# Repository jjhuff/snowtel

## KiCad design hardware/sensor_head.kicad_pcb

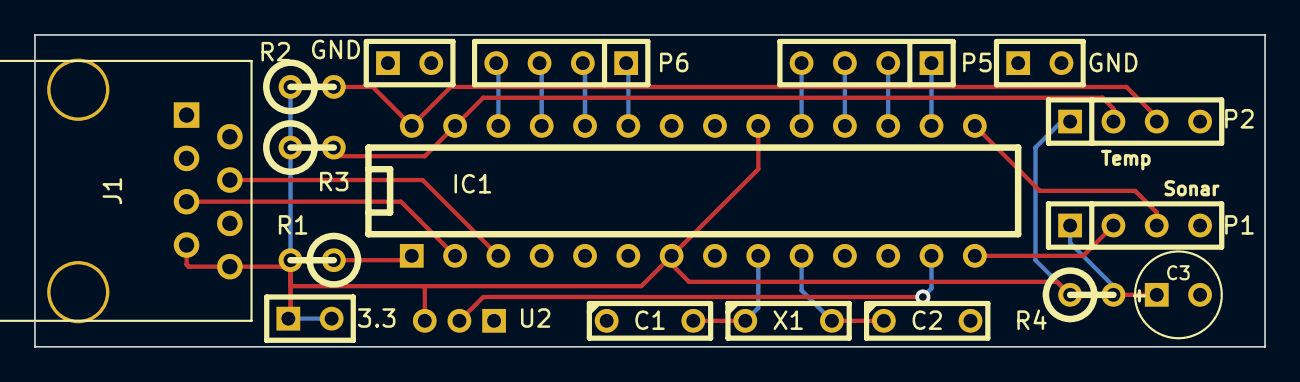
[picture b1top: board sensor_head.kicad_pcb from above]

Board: 2 copper layers, 72.1 x 18.3 mm, 18 parts (0 on the bottom side), 21 nets.

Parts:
3.3: CONN_2; SIL-2
C1, C2: 22pF; C2
C3: C1V5
GND: CONN_2; SIL-2
GND#2: CONN_2; SIL-2
IC1: DIP-28__300
J1: RJ45_8
P1, P2, P5, P6: CONN_4; SIL-4
R1: 10k; R1
R2, R3: 2.2k; R1
R4: 10; R1
U2: TO92-INLINE
X1: 16MHz; C2

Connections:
+3.3V: 3.3.1, 3.3.2, IC1.7, IC1.20, J1.7, J1.8, P2.1, R1.2, R2.1, R3.1, R4.1, U2.3
GND: C1.1, C2.2, C3.2, GND.1, GND.2, GND#2.1, GND#2.2, IC1.8, IC1.22, J1.1, J1.2, P1.4, P2.4, U2.1
unnamed: IC1.14, P1.2
unnamed: IC1.27, P2.2, R3.2
unnamed: IC1.28, P2.3, R2.2
unnamed: IC1.1, R1.1
unnamed: IC1.3, J1.4
unnamed: IC1.2, J1.5
unnamed: C3.1, P1.1, R4.2
unnamed: IC1.15, P1.3
unnamed: C2.1, IC1.10, X1.2
unnamed: C1.2, IC1.9, X1.1
unnamed: IC1.18, P5.3
unnamed: IC1.19, P5.4
unnamed: IC1.23, P6.1
unnamed: IC1.24, P6.2
unnamed: IC1.25, P6.3
unnamed: IC1.26, P6.4
unnamed: IC1.17, P5.2
unnamed: IC1.13, U2.2
unnamed: IC1.16, P5.1

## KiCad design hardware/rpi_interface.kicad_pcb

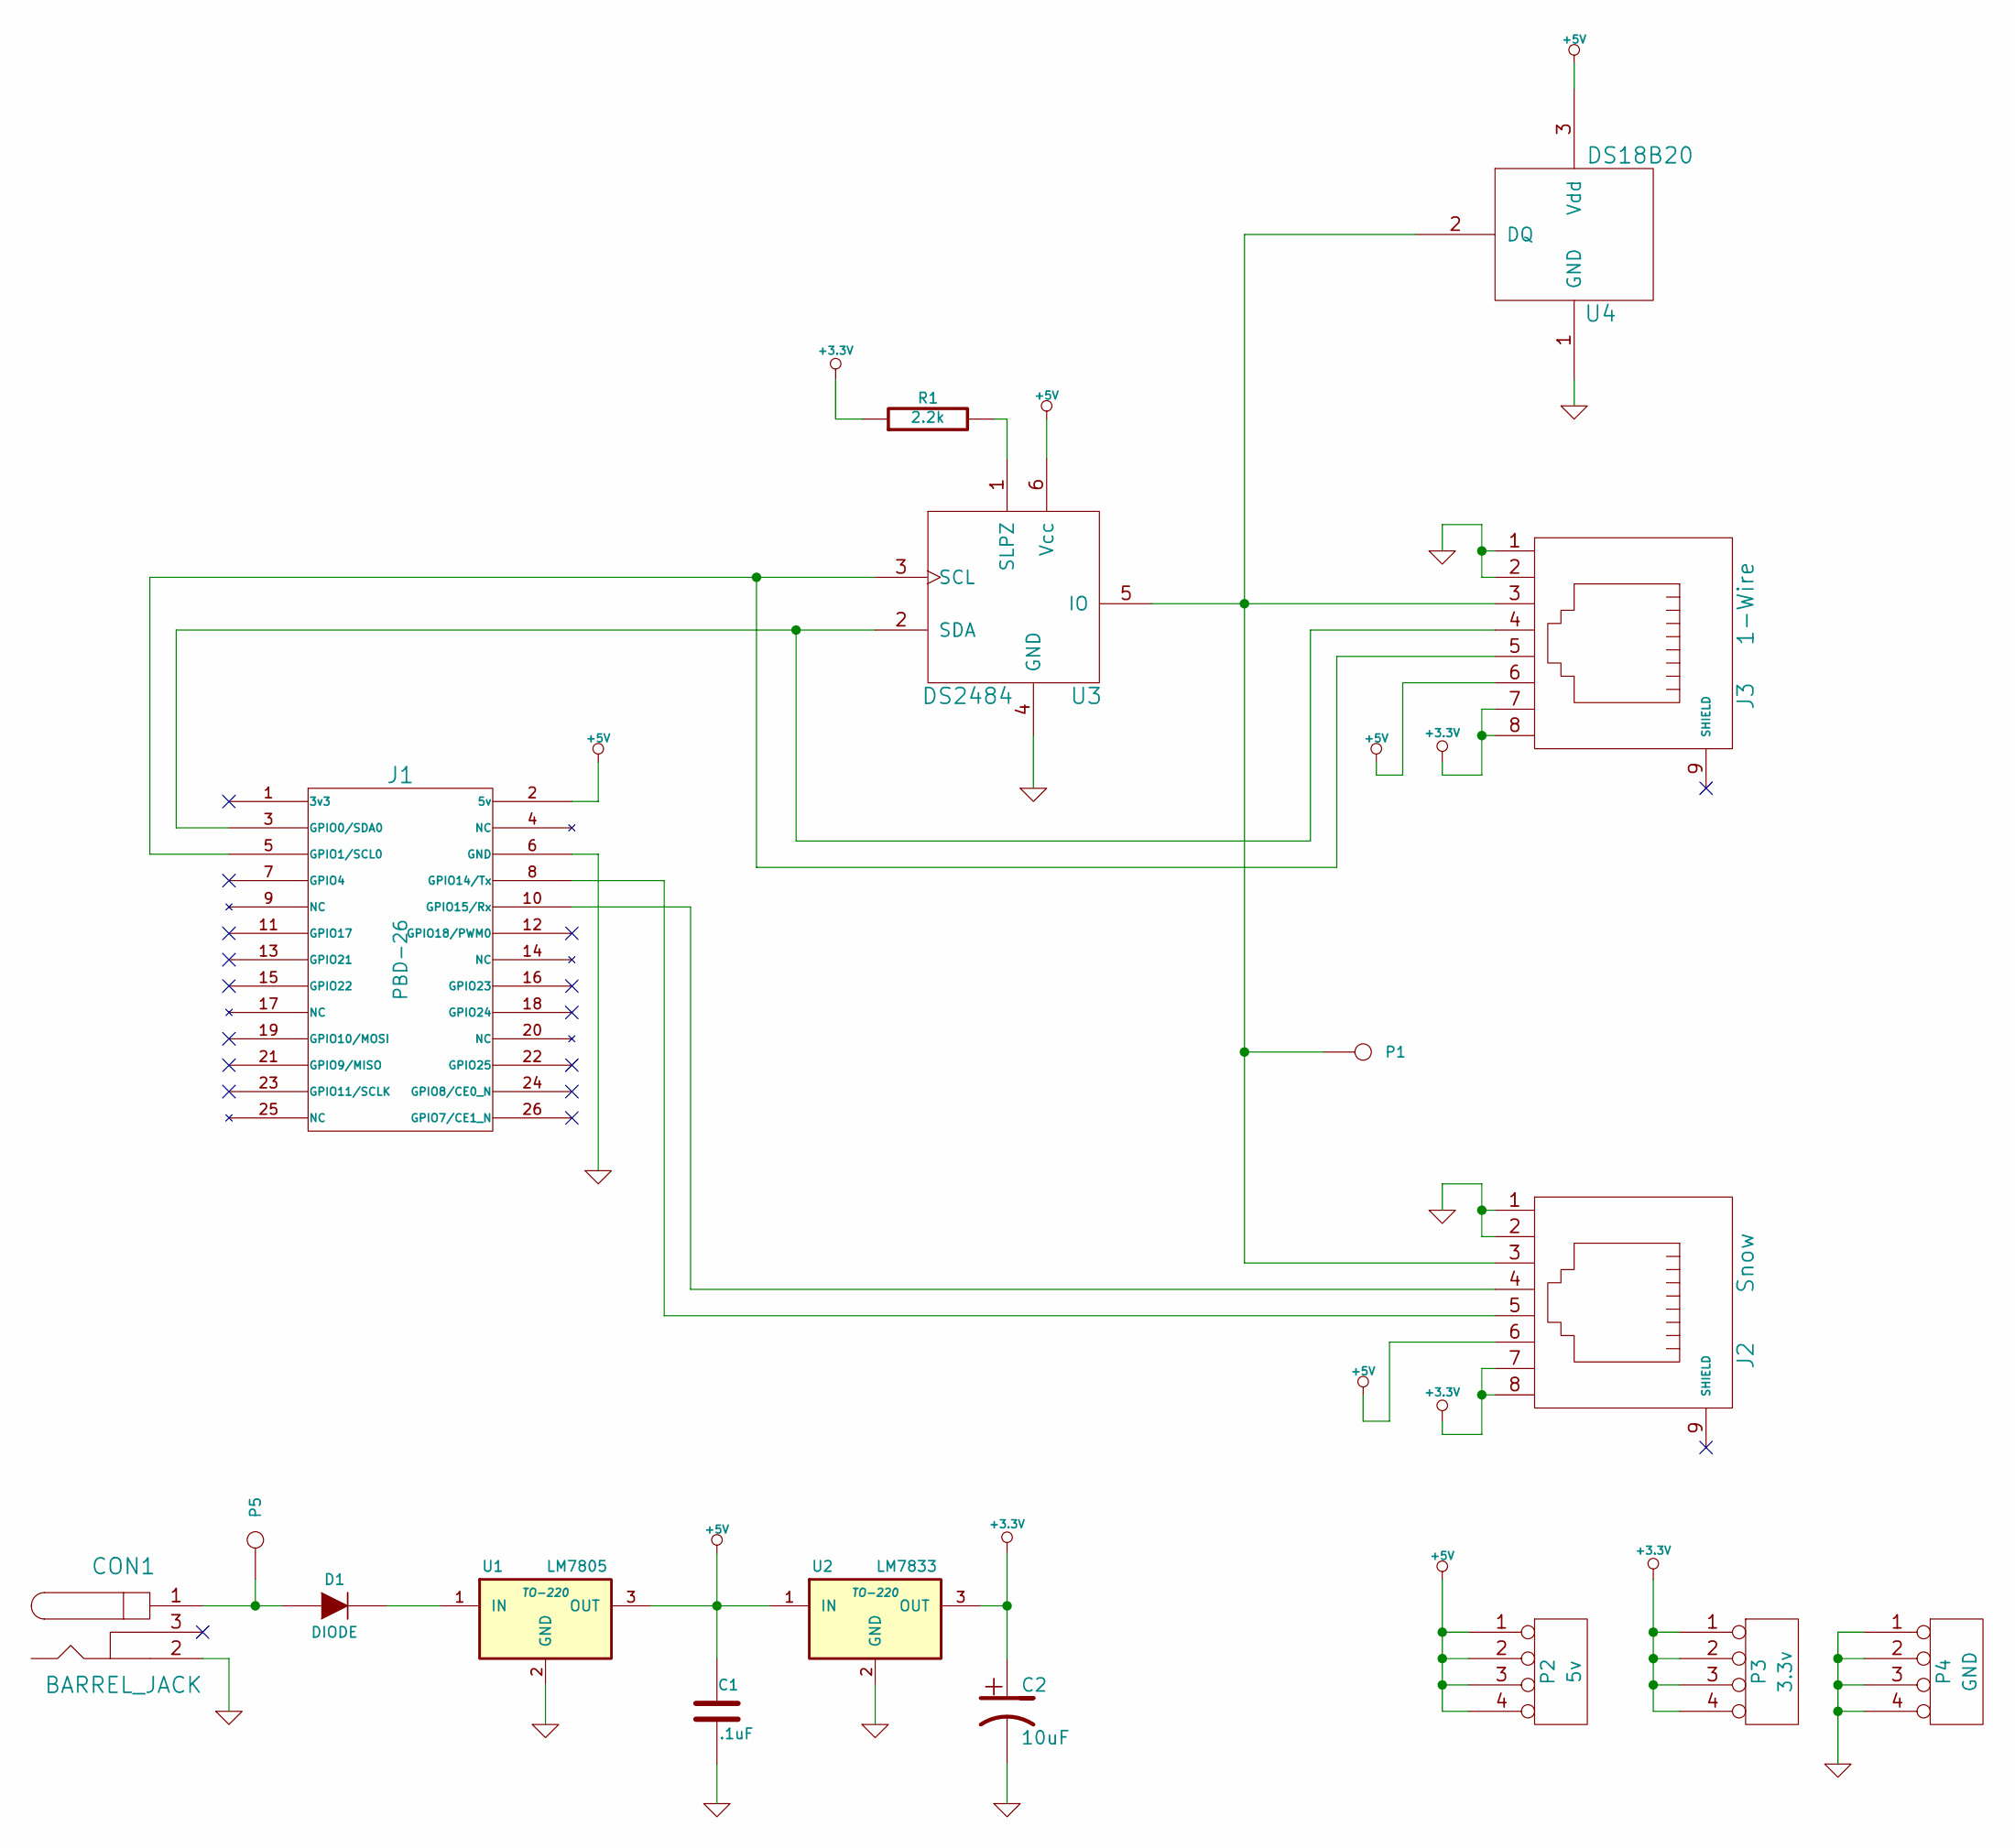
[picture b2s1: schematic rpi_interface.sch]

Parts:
C1: .1uF
C2: 10uF
CON1: BARREL_JACK
D1: DIODE
J1: PBD-26
J2: Snow
J3: 1-Wire
P1: 1-Wire
P2: 5v
P3: 3.3v
P4: GND
P5: CONN_1
R1: 2.2k
U1: LM7805; TO-220
U2: LM7833; TO-220
U3: DS2484
U4: DS18B20

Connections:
+3.3V: C2.1, J2.7, J2.8, J3.7, J3.8, P3.1, P3.2, P3.3, P3.4, R1.1, U2.3 (OUT)
+5V: C1.1, J1.2 (5v), J2.6, J3.6, P2.1, P2.2, P2.3, P2.4, U1.3 (OUT), U2.1 (IN), U3.6 (Vcc), U4.3 (Vdd)
GND: C1.2, C2.2, CON1.2, J1.6 (GND), J2.1, J2.2, J3.1, J3.2, P4.1, P4.2, P4.3, P4.4, U1.2 (GND), U2.2 (GND), U3.4 (GND), U4.1 (GND)
unnamed: CON1.1, D1.1 (A), P5.1
unnamed: D1.2 (K), U1.1 (IN)
unnamed: J1.8 (GPIO14/Tx), J2.5
unnamed: J1.10 (GPIO15/Rx), J2.4
unnamed: J1.3 (GPIO0/SDA0), J3.4, U3.2 (SDA)
unnamed: J1.5 (GPIO1/SCL0), J3.5, U3.3 (SCL)
unnamed: J2.3, J3.3, P1.1, U3.5 (IO), U4.2 (DQ)
unnamed: R1.2, U3.1 (SLPZ)

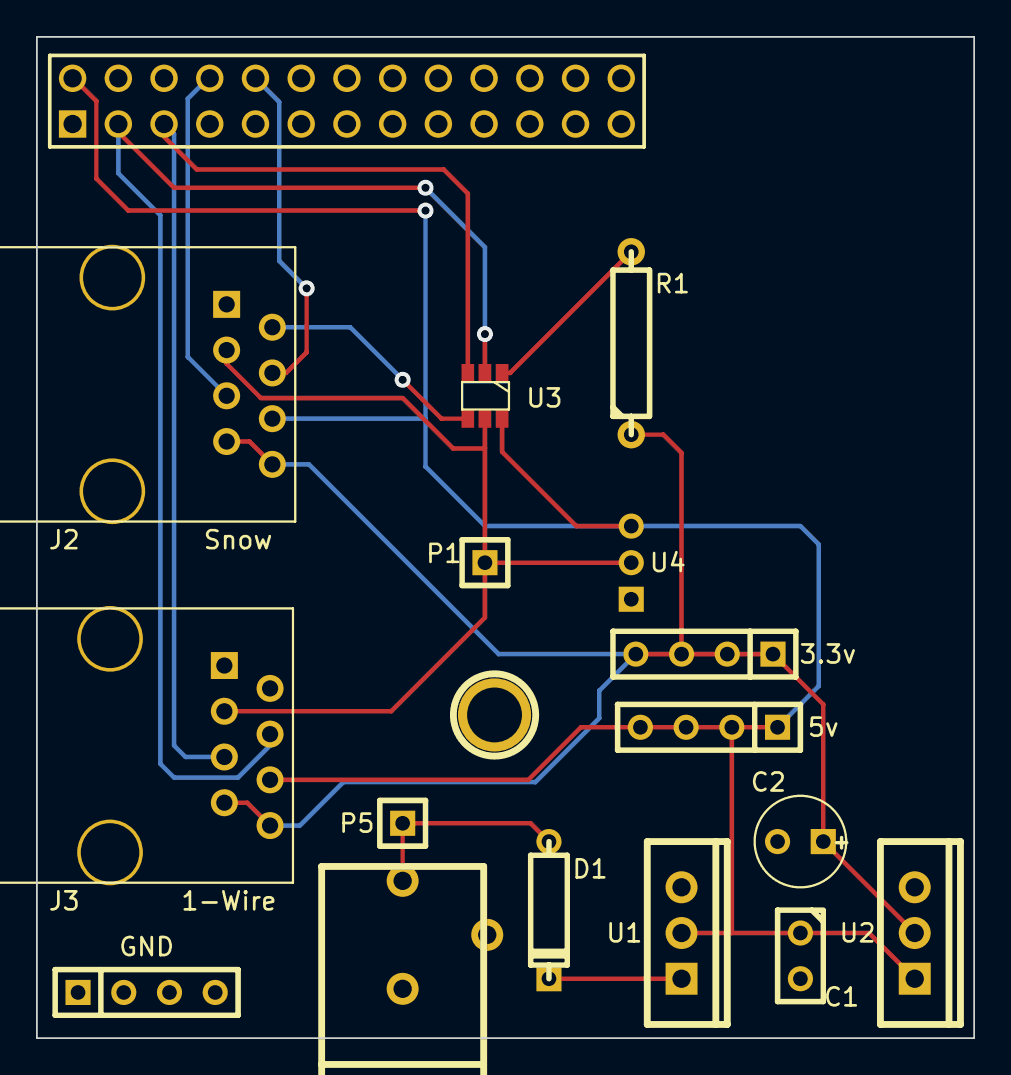
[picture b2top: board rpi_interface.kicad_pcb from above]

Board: 2 copper layers, 52.1 x 55.6 mm, 17 parts (0 on the bottom side), 11 nets.

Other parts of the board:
M1: 1pin

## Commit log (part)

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2012-10-09 IR temp sensor working
2012-10-09 Remove useless file
2012-10-09 Gitignore some stuff
2012-10-10 sonar working
2012-10-19 Upgrade option to transfer to the bootloader
2012-10-20 Show time of flight for distance
2012-10-20 Move stuff to a firmware dir
2012-10-20 Show the temp in celsius
2012-10-23 Zero pulse length so we know when we didn't read. Speed up auto-mode
2012-10-24 Starting web UI
2012-10-24 Remove units from output
2012-10-26 Better handling of missing data
2012-10-26 List sensors and readings
2012-10-26 fix index
2012-10-26 table column headers
2012-10-26 Use google annotated timeline to show data
2012-10-26 Fix sacles
2012-10-26 Request all readings instead of the last 24hrs
2012-10-26 Sensor name and back link
2012-10-26 Show current readings on the homepage
2012-10-26 Use sensor height for snow depth calculation
2012-10-26 Take a new sensors first reading as it's height
2012-10-26 Improve commandline options. Choose sensor ID based on eth0 MAC
2012-10-26 Fix rate option
2012-10-31 Switch to the maxbotix sensor
2012-11-03 Switch to seperate graphs for temps and height
2012-11-03 sort the data before charting
2012-11-03 Remove debug code
2012-11-04 Snow Height -> Snow Depth
2012-11-04 Cache sensor readings
2012-11-04 build sensor list in JS so we can do consistant unit conversion
2012-11-05 tweak some graph options
2012-11-10 ability to filter snow height
2012-11-10 remove auto_now from timestamp so it is created time
2012-11-10 Allow merging of sensor readings
2012-11-10 fix merge index dir
2012-11-12 Code to build scatter charts
2012-11-12 Snow height error logging
2012-11-12 Add sample data
2012-11-17 Update for new sensor
2012-11-19 Format tooltip data
2012-11-22 Correct height measurement for temp
2012-11-22 Add a moving average filter to depth data
2012-11-25 Refactor JS into seperate files
2012-11-25 Unit conversion
2012-11-25 Remove current readings from index page
2012-11-28 send time of flight to the server as well
2012-11-28 Improve distance temperature correction
2012-11-29 Disable filter. Fix time format
2012-11-29 Ensure sorted data
2012-11-29 Insert breaks in the graph for breaks in the data
2012-11-29 Attempt to handle nulls in the filter
2012-11-29 remove debug logs
2012-11-30 Add a 8s watchdog to prevent badness
2012-11-30 Ignore invalid data
2012-12-01 update test data
2012-12-01 Filtering!
2012-12-01 7days by default. Fix scale
2012-12-02 remove old snow_height field
2012-12-02 Add webcam and current conditions
2012-12-02 Record & report weather station temp
2012-12-07 ignore negative snow depths
2012-12-08 Fix reporting when snow data is sporadic. Handle AVR reboots
2012-12-20 Tool to remove snow readings in a time range
2013-02-02 When processing a cache miss, only fetch 30days of data
2013-10-13 add softuart
2013-10-16 Fix tabs
2013-10-16 Add support for reading from sonar via serial
2013-10-22 Add support for a 1wire temp sensors on PD7
2013-10-31 new hardware designs
2013-11-12 hardware bugs list
2013-11-12 Updates from the field
2013-11-15 rasbian os mods
2013-11-18 Fix for new app engine dev server
2013-11-20 Fix ds18b20 temp conversion
2013-11-20 Fix line endings
2013-11-21 Disable data filtering and fixed axes
2013-11-21 Test code for webcam/laster distance
2013-11-25 Bugs for the rpi interface board
2013-12-01 Make the enclosure sensor optional
2013-12-02 Re-add some utility requests
2013-12-02 Display weather station temp if available
2014-01-02 Add a module for batch jobs. Creat an export job
2014-01-02 Add the last updated timestamp
2014-02-11 Sensor head schematic updates
2014-10-20 Updated for new googler cloud sdk
2014-10-20 Tool to remove sensor data
2014-10-31 test spark firmware
2014-10-31 Working on go converstion #2
2014-11-03 Mostly working read-only
2014-11-03 Improve layout
2014-11-03 Set proper app name when deploying
2014-11-03 Fix JS syntax
2014-11-04 Change dev app name
2014-11-04 Refresh every 5min
2014-11-08 Refresh without reloading all of the data
2014-11-09 Fix memory leak
2014-11-10 Basic posting of reading data
2014-11-12 Pull weather station temp from WeatherUnderground
2014-11-12 Create missing sensors
2014-11-12 Remove legazy API
2014-11-12 Remove old python code
2014-11-14 Try to fix non-updating current readings
2014-11-22 Add weather station temp and make text and graph consistant
2015-01-04 APIs to delete readings and update sensor info
2015-01-04 Experiment with a long median filter
2015-11-08 deploy fixes
2015-11-17 Add station temp
2015-11-18 Fix deploy on Arch
2015-11-18 Util endpoint to adjust height
2015-11-18 Add support for lidar signal strength
2015-11-18 Disable filtering
2015-11-22 Return early on parse error
2015-12-09 Filter out bad weather station temps
2015-12-09 Only adjust sensors with the specified height
2016-12-18 Allow nullable fields
2017-11-21 Hide cols
2017-11-21 Add before/after filters for delete
2017-11-23 Improve filterin
2020-12-21 Reworking to modern stack
2020-12-22 Initial sensor API requests
2020-12-22 SPA serving support
2020-12-22 Load readings
2020-12-23 Improve package install
2020-12-28 Basic graphing!
2020-12-29 Deployable
2020-12-29 Imperial units
2020-12-29 Add temp charts
2020-12-29 Refresh intervale
2020-12-29 Fix timestamp
2020-12-29 async and enable debug mode
2020-12-29 production mode
2020-12-30 Fix prod build
2020-12-30 Fix refreshing
2020-12-31 Switch to webhook for data updates
2020-12-31 Add cloudbuild.yaml
2021-01-12 set scale
2021-05-10 Bump url-parse from 1.4.7 to 1.5.1 in /js
    Bumps [url-parse](https://github.com/unshiftio/url-parse) from 1.4.7 to 1.5.1.
    - [Release notes](https://github.com/unshiftio/url-parse/releases)
    - [Commits](https://github.com/unshiftio/url-parse/compare/1.4.7...1.5.1)
2021-05-11 Bump lodash from 4.17.20 to 4.17.21 in /js
    Bumps [lodash](https://github.com/lodash/lodash) from 4.17.20 to 4.17.21.
    - [Release notes](https://github.com/lodash/lodash/releases)
    - [Commits](https://github.com/lodash/lodash/compare/4.17.20...4.17.21)
2021-05-12 Bump postcss from 8.2.1 to 8.2.10 in /js
    Bumps [postcss](https://github.com/postcss/postcss) from 8.2.1 to 8.2.10.
    - [Release notes](https://github.com/postcss/postcss/releases)
    - [Changelog](https://github.com/postcss/postcss/blob/main/CHANGELOG.md)
    - [Commits](https://github.com/postcss/postcss/compare/8.2.1...8.2.10)
2021-05-29 Bump dns-packet from 1.3.1 to 1.3.4 in /js
    Bumps [dns-packet](https://github.com/mafintosh/dns-packet) from 1.3.1 to 1.3.4.
    - [Release notes](https://github.com/mafintosh/dns-packet/releases)
    - [Changelog](https://github.com/mafintosh/dns-packet/blob/master/CHANGELOG.md)
    - [Commits](https://github.com/mafintosh/dns-packet/compare/v1.3.1...v1.3.4)
2021-06-06 Bump ws from 6.2.1 to 6.2.2 in /js
    Bumps [ws](https://github.com/websockets/ws) from 6.2.1 to 6.2.2.
    - [Release notes](https://github.com/websockets/ws/releases)
    - [Commits](https://github.com/websockets/ws/commits)
    ---
    updated-dependencies:
    - dependency-name: ws
2021-08-12 Bump path-parse from 1.0.6 to 1.0.7 in /js
    Bumps [path-parse](https://github.com/jbgutierrez/path-parse) from 1.0.6 to 1.0.7.
    - [Release notes](https://github.com/jbgutierrez/path-parse/releases)
    - [Commits](https://github.com/jbgutierrez/path-parse/commits/v1.0.7)
    ---
    updated-dependencies:
    - dependency-name: path-parse
2021-10-06 Bump url-parse from 1.4.7 to 1.5.3 in /js
    Bumps [url-parse](https://github.com/unshiftio/url-parse) from 1.4.7 to 1.5.3.
    - [Release notes](https://github.com/unshiftio/url-parse/releases)
    - [Commits](https://github.com/unshiftio/url-parse/compare/1.4.7...1.5.3)
    ---
    updated-dependencies:
    - dependency-name: url-parse
2022-01-22 Bump nanoid from 3.1.20 to 3.2.0 in /js
    Bumps [nanoid](https://github.com/ai/nanoid) from 3.1.20 to 3.2.0.
    - [Release notes](https://github.com/ai/nanoid/releases)
    - [Changelog](https://github.com/ai/nanoid/blob/main/CHANGELOG.md)
    - [Commits](https://github.com/ai/nanoid/compare/3.1.20...3.2.0)
    ---
    updated-dependencies:
2022-02-13 Bump follow-redirects from 1.13.1 to 1.14.8 in /js
    Bumps [follow-redirects](https://github.com/follow-redirects/follow-redirects) from 1.13.1 to 1.14.8.
    - [Release notes](https://github.com/follow-redirects/follow-redirects/releases)
    - [Commits](https://github.com/follow-redirects/follow-redirects/compare/v1.13.1...v1.14.8)
    ---
    updated-dependencies:
    - dependency-name: follow-redirects
2022-02-19 Bump url-parse from 1.4.7 to 1.5.7 in /js
    Bumps [url-parse](https://github.com/unshiftio/url-parse) from 1.4.7 to 1.5.7.
    - [Release notes](https://github.com/unshiftio/url-parse/releases)
    - [Commits](https://github.com/unshiftio/url-parse/compare/1.4.7...1.5.7)
    ---
    updated-dependencies:
    - dependency-name: url-parse
2022-03-28 Bump minimist from 1.2.5 to 1.2.6 in /js
    Bumps [minimist](https://github.com/substack/minimist) from 1.2.5 to 1.2.6.
    - [Release notes](https://github.com/substack/minimist/releases)
    - [Commits](https://github.com/substack/minimist/compare/1.2.5...1.2.6)
    ---
    updated-dependencies:
    - dependency-name: minimist
2022-04-29 Bump async from 2.6.3 to 2.6.4 in /js
    Bumps [async](https://github.com/caolan/async) from 2.6.3 to 2.6.4.
    - [Release notes](https://github.com/caolan/async/releases)
    - [Changelog](https://github.com/caolan/async/blob/v2.6.4/CHANGELOG.md)
    - [Commits](https://github.com/caolan/async/compare/v2.6.3...v2.6.4)
    ---
    updated-dependencies:
2022-06-01 Bump eventsource from 1.0.7 to 1.1.1 in /js
    Bumps [eventsource](https://github.com/EventSource/eventsource) from 1.0.7 to 1.1.1.
    - [Release notes](https://github.com/EventSource/eventsource/releases)
    - [Changelog](https://github.com/EventSource/eventsource/blob/master/HISTORY.md)
    - [Commits](https://github.com/EventSource/eventsource/compare/v1.0.7...v1.1.1)
    ---
    updated-dependencies:
2022-07-20 Bump terser from 4.8.0 to 4.8.1 in /js
    Bumps [terser](https://github.com/terser/terser) from 4.8.0 to 4.8.1.
    - [Release notes](https://github.com/terser/terser/releases)
    - [Changelog](https://github.com/terser/terser/blob/master/CHANGELOG.md)
    - [Commits](https://github.com/terser/terser/commits)
    ---
    updated-dependencies:
2022-11-10 Bump minimatch from 3.0.4 to 3.1.2 in /js
    Bumps [minimatch](https://github.com/isaacs/minimatch) from 3.0.4 to 3.1.2.
    - [Release notes](https://github.com/isaacs/minimatch/releases)
    - [Commits](https://github.com/isaacs/minimatch/compare/v3.0.4...v3.1.2)
    ---
    updated-dependencies:
    - dependency-name: minimatch
2022-11-16 Bump loader-utils from 1.4.0 to 1.4.2 in /js
    Bumps [loader-utils](https://github.com/webpack/loader-utils) from 1.4.0 to 1.4.2.
    - [Release notes](https://github.com/webpack/loader-utils/releases)
    - [Changelog](https://github.com/webpack/loader-utils/blob/v1.4.2/CHANGELOG.md)
    - [Commits](https://github.com/webpack/loader-utils/compare/v1.4.0...v1.4.2)
    ---
    updated-dependencies:
2022-12-07 Bump decode-uri-component from 0.2.0 to 0.2.2 in /js
    Bumps [decode-uri-component](https://github.com/SamVerschueren/decode-uri-component) from 0.2.0 to 0.2.2.
    - [Release notes](https://github.com/SamVerschueren/decode-uri-component/releases)
    - [Commits](https://github.com/SamVerschueren/decode-uri-component/compare/v0.2.0...v0.2.2)
    ---
    updated-dependencies:
    - dependency-name: decode-uri-component
